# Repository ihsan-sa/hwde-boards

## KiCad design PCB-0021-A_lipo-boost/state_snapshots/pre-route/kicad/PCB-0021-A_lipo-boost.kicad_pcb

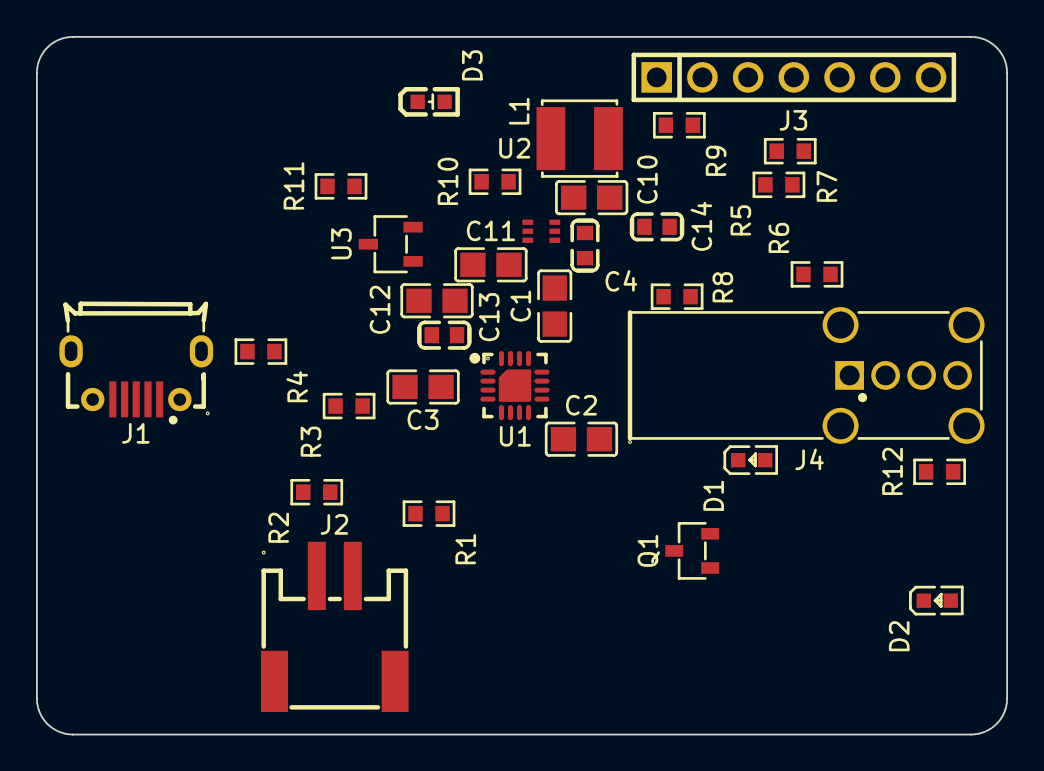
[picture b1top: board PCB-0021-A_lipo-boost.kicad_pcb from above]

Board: 2 copper layers, 53.9 x 38.8 mm, 33 parts (0 on the bottom side), 21 nets, no tracks yet.

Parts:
C1: 4.7uF 25V X5R; C0805
C2, C3, C10: 10uF 25V X5R; C0805
C4, C13, C14: 100nF 50V X7R; C0603
C11, C12: 22uF 25V X5R; C0805
D1: ORH-R36A orange; LED0603-RD
D2: KT-0603G green; LED0603-RD
D3: KT-0603R red; LED-SMD_L1.6-W0.8-R-RD
J1: MicroXNJ; MICRO-USB-SMD_MICROXNJ_1
J2: S2B-PH-SM4-TB(LF)(SN); CONN-SMD_P2.00_S2B-PH-SM4-TB-LF-SN
J3: HX PZ2.54-1x7P; HDR-TH_7P-P2.54-V-M
J4: Type-A-AF90; USB-A-TH_U-A-24DD-Y-13
L1: 1uH; IND-SMD_L4.0-W4.0
Q1: 2N7002; SOT-23-3_L2.9-W1.3-P1.90-LS2.4-BR
R1: 10k; R0603
R2: 1.2k; R0603
R3, R5, R7: 1k; R0603
R4: 51k; R0603
R6: 470R; R0603
R8, R9, R11: 100k; R0603
R10: 732k; R0603
R12: 0R; R0603
U1: BQ24074RGTR; QFN-16_L3.0-W3.0-P0.50-TL-EP1.7
U2: TPS61023DRLR; SOT-563_L1.6-W1.2-P0.50-LS1.6-BR
U3: MSXC61CN3302MR; SOT-23-3_L2.9-W1.6-P1.90-LS2.8-BR

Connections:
+5V: C11.1, C12.1, C13.1, J3.4, J4.1, R10.1, U2.6
+SYS: C2.1, C10.1, C14.1, J3.3, L1.1, R5.1, R6.1, R7.1, R8.1, R9.1, U1.5, U1.10, U1.11, U2.3
/CHG: D1.1, Q1.1, R8.2, U1.9
/CHG_A: D1.2, R5.2
/DONE_A: D2.2, R6.2
/DONE_K: D2.1, Q1.3
/EN: J3.6, R9.2, U2.2
/FB: R10.2, R11.1, U2.1
/ILIM: R2.1, U1.12
/ISET: R3.1, U1.16
/LBO: D3.2, J3.5, U3.1
/LB_A: D3.1, R7.2
/PGOOD: Q1.2, U1.7
/SW: L1.2, U2.5
/TMR: R4.1, U1.14
/TS: R1.1, U1.1
/USB_DM: J4.2, R12.2
/USB_DP: J4.3, R12.1
GND: C1.2, C2.2, C3.2, C4.2, C10.2, C11.2, C12.2, C13.2, C14.2, J1.5, J1.6, J1.7, J1.8, J1.9, J2.2, J3.1, J3.7, J4.4, J4.5, J4.6, R1.2, R2.2, R3.2, R4.2, R11.2, U1.4, U1.6, U1.8, U1.17, U2.4, U3.2
VBAT: C3.1, J2.1, J3.2, U1.2, U1.3, U3.3
VBUS: C1.1, C4.1, J1.1, U1.13
